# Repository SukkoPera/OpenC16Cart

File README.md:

# OpenC16Cart

OpenC16Cart is an Open Hardware 8/16/32/64 KB Cartridge for the Commodore 16, Plus/4 and the rest of the Commodore 264 family.

## Summary
> Like all the other Commodore 8-bit systems, the Plus/4 had a cartridge port for ROM-based software. Because the computer did not do well in the marketplace, however, very few were released. - Bo Zimmerman

One day I decided to fix my old Commodore 16. I found out about [Diag264](http://www.inchocks.co.uk/commodore/Diag264/) and, since I knew that C16 carts weren't exactly common (to this very day of 2026 I have never seen one "in the flesh"!), I was shocked to learn that [people are deliberately destroying genuine carts to use them as donors to build a Diag264](http://blog.tynemouthsoftware.co.uk/2014/03/commodore-264-c16-and-plus-4-diagnostic.html).

Since I had already built an [Open Hardware cartridge for the Commodore 64](https://github.com/SukkoPera/OpenC64Cart), I thought that one for the C16 could not be much different, and so this project was born.

Since I did not own a cartridge, I set out to find images of PCBs of real cartridges on the Net, only to find out that those are rare as well. In the end I found a couple of [top](https://github.com/SukkoPera/OpenC16Cart/blob/master/doc/inspiration-top.jpg)+[bottom](https://github.com/SukkoPera/OpenC16Cart/blob/master/doc/inspiration-bottom.jpg) images, and started to reverse engineer the design from those. With the help of [some service manuals](http://www.zimmers.net/anonftp/pub/cbm/schematics/computers/plus4/index.html), I came up with OpenC16Cart. I then expanded it to have the ability of using bigger (E(E))PROMs which could store multiple ROM images.

With V5, I even added the possibility of having a single-EEPROM 64 kB cartridge spanning both the C1 and C2 slots.

> [!IMPORTANT]
> V5 is a 44-pin cartridge. It is not compatible with a stock C16/+4. To use it, you will need a [Plus4MultiExpander](https://github.com/SukkoPera/Plus4MultiExpander) [^v4].

V5 was designed in order to fit into [TFW8b's Stumpy Cases](https://www.tfw8b.com/product/commodore-c64-stumpy-cartridge-case/), but the actual fitting has never been checked.

## Configuration
As of V5, OpenC16Cart might work in different modes. Ideally, the cartridge is used with a 64 kb EEPROM, in which case the following configurations will be available:

### 16 kB Mode
In 16 kB mode, you get 4 banks, which can be selected through appropriate placement of the SW2 and SW3 jumpers:

|Bank|SW3|SW2|ROM Area   |
|----|---|---|-----------|
|0   |LO |LO |$0000-$3fff|
|1   |LO |HI |$4000-$7fff|
|2   |HI |LO |$8000-$bfff|
|3   |HI |HI |$c000-$ffff|

Note that the cartridge will respond to all C1 and C2 low/high slots. If this is unwanted, cut open JP1/2/3 accordingly (or do not mount D1/2/3). Also note there is no way to respond to a single C2 slot.

### 32 kB Mode
In 32 kB mode, SW2 must be placed in the `DIR` position and 2 banks will be available through manipulation of SW3:

|Bank|SW3|ROM Area                                      |
|----|---|----------------------------------------------|
|0   |LO |Low ROM: $0000-$3fff<br/>High ROM: $4000-$7fff|
|1   |HI |Low ROM: $8000-$bfff<br/>High ROM: $c000-$ffff|

As in 16 kB mode, you might want to play with the jumpers or diodes.

### 64 kB Mode
In 64 kB mode, both SW2 and SW3 must be placed in the `DIR` position and, obviously, only a single bank will be available.

|Bank|ROM Area                                                                                                    |
|----|------------------------------------------------------------------------------------------------------------|
|0   |C2 Low ROM: $0000-$3fff<br/>C2 High ROM: $4000-$7fff<br>C1 Low ROM: $8000-$bfff<br/>C1 High ROM: $c000-$ffff|

Note that **C2 goes first**.

## Releases
If you want to get this board produced, you are recommended to get [the latest release](https://github.com/SukkoPera/OpenC16Cart/releases) rather than the current git version, as the latter might be under development and is not guaranteed to be working.

Every release is accompanied by its Bill Of Materials (BOM) file and any relevant notes about it, which you are recommended to read carefully.

**I am not providing ready-to-use gerber files**. If all you want is **to get boards made, I would really appreciate if you did so [in a way that supports the project](#support-the-project)**.

## License
The OpenC16Cart documentation, including the design itself, is copyright &copy; SukkoPera 2019-2026 and is licensed under the [Creative Commons Attribution-NonCommercial-ShareAlike 4.0 International License](https://creativecommons.org/licenses/by-nc-sa/4.0/).

This documentation is distributed *as is* and WITHOUT ANY EXPRESS OR IMPLIED WARRANTIES whatsoever with respect to its functionality, operability or use, including, without limitation, any implied warranties OF MERCHANTABILITY, SATISFACTORY QUALITY, FITNESS FOR A PARTICULAR PURPOSE or infringement. We expressly disclaim any liability whatsoever for any direct, indirect, consequential, incidental or special damages, including, without limitation, lost revenues, lost profits, losses resulting from business interruption or loss of data, regardless of the form of action or legal theory under which the liability may be asserted, even if advised of the possibility or likelihood of such damages.

## Support the Project
If you want to get some boards manufactured, you can get them from PCBWay through this link:

You get my gratitude and cheap, professionally-made and good quality PCBs, I get some credit that will help with this and [other projects](https://www.pcbway.com/project/member/shareproject/?bmbid=41100). You won't even have to worry about the various PCB options, it's all pre-configured for you!

Also, if you still have to register, [you can use this link](https://www.pcbway.com/setinvite.aspx?inviteid=41100) to get some bonus initial credit (and yield me some more).

You can also buy me a coffee if you want:

[^v4]: Although this *might* be amended at some point, that's why there currently is no V4, it was reserved for that.

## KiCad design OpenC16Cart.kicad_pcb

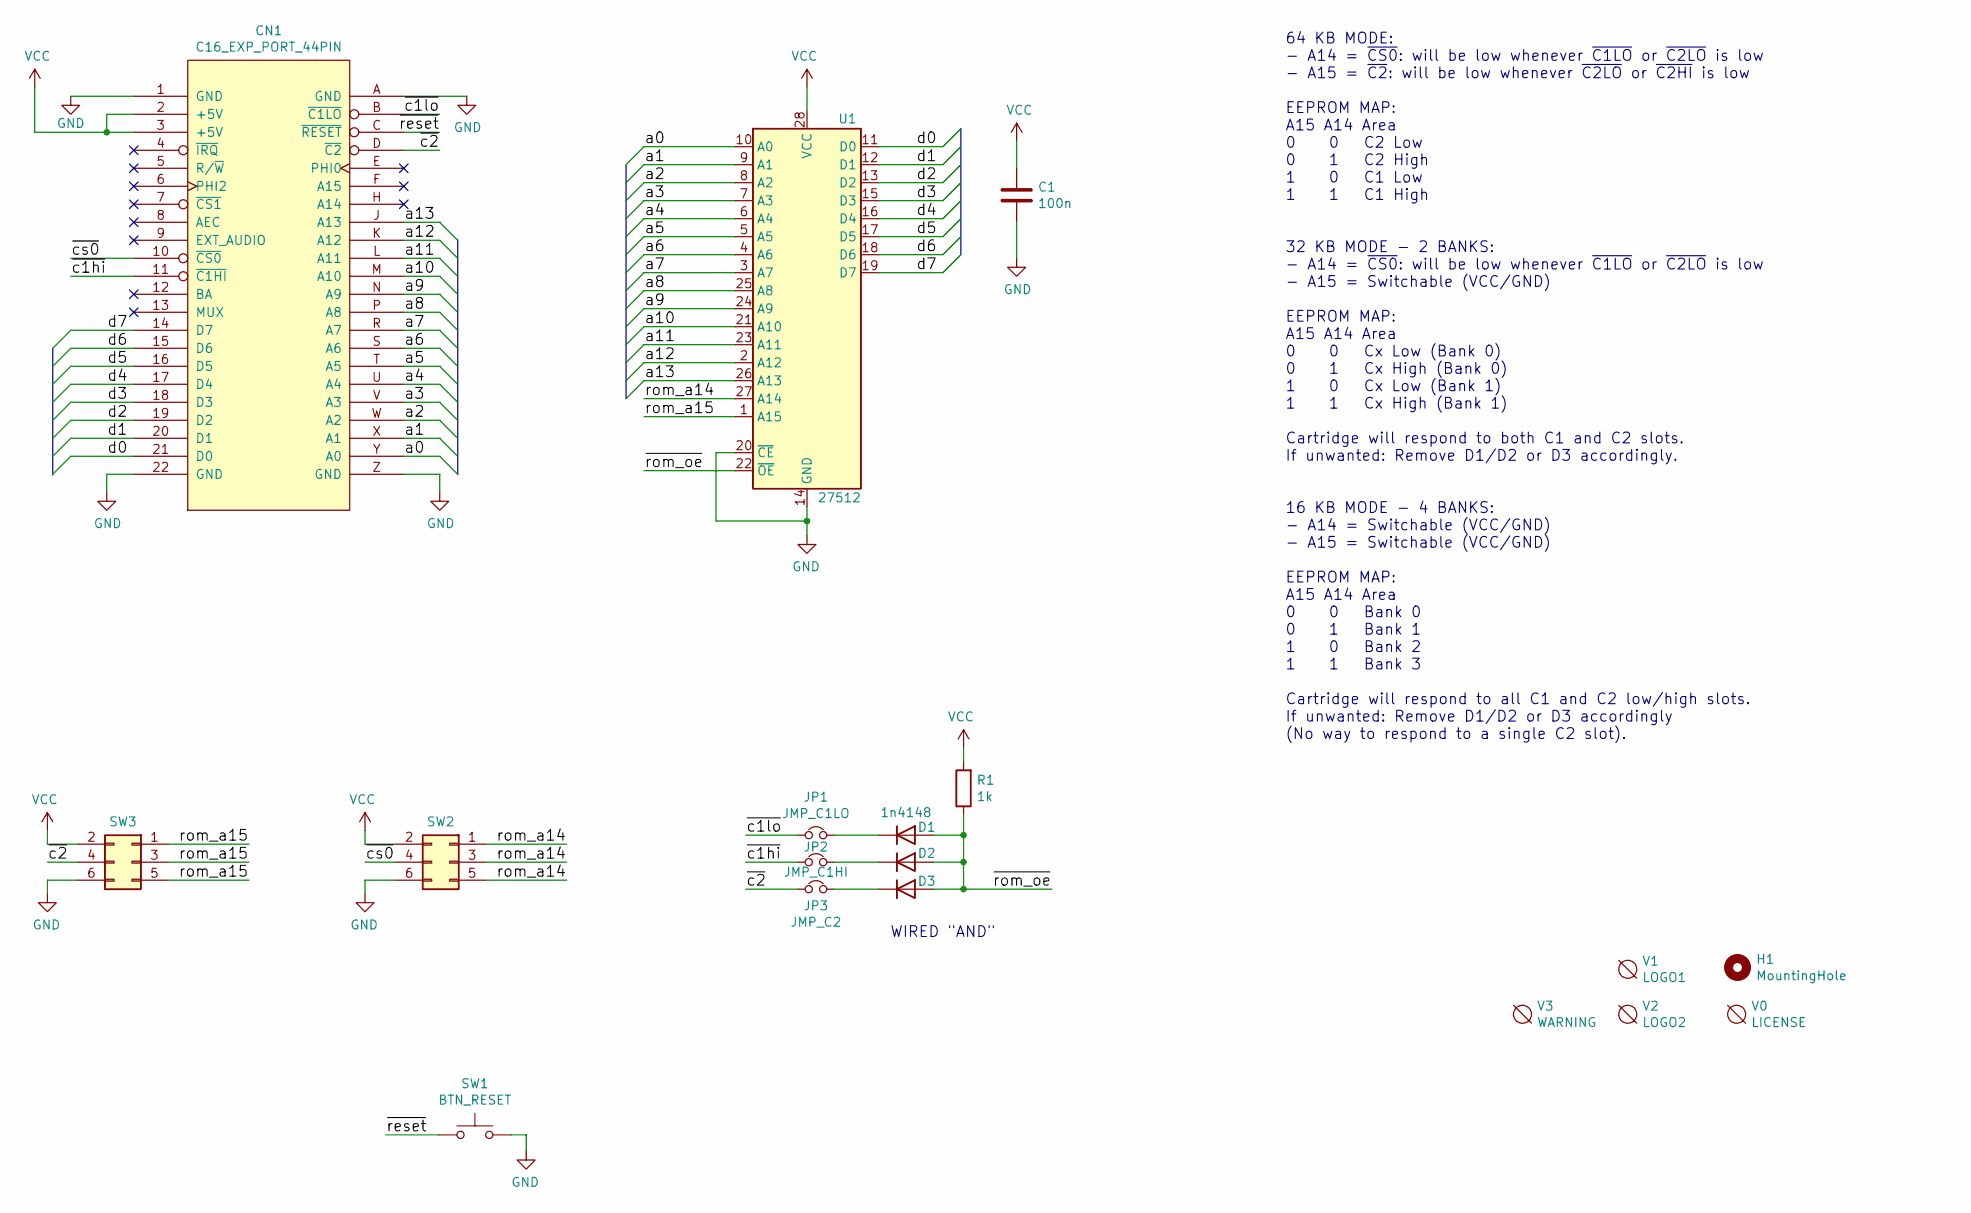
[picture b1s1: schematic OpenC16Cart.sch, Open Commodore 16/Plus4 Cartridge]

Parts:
C1: 100n; C_Disc_D7.0mm_W2.5mm_P5.00mm
CN1: C16_EXP_PORT_44PIN; C16-Exp-Port-44Pin
D1, D2, D3: 1n4148; D_DO-35_SOD27_P7.62mm_Horizontal
H1: MountingHole; MountingHole_5mm
JP1: JMP_C1LO; SolderJumper-2_P1.3mm_Bridged_RoundedPad1.0x1.5mm
JP2: JMP_C1HI; SolderJumper-2_P1.3mm_Bridged_RoundedPad1.0x1.5mm
JP3: JMP_C2; SolderJumper-2_P1.3mm_Bridged_RoundedPad1.0x1.5mm
R1: 1k; R_Axial_DIN0204_L3.6mm_D1.6mm_P7.62mm_Horizontal
SW1: BTN_RESET; SW_PUSH_6mm_H8mm
SW2, SW3: Conn_02x03_Odd_Even; PinHeader_2x03_P2.54mm_Vertical
U1: 27512; DIP-28_W15.24mm_Socket_LongPads
V0: LICENSE; cc_by_nc_sa
V1: LOGO1; logo1
V2: LOGO2; logo2
V3: WARNING; Logo_silk_warning_10x8.5mm

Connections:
/a0: CN1.Y (A0), U1.10 (A0)
/a1: CN1.X (A1), U1.9 (A1)
/a2: CN1.W (A2), U1.8 (A2)
/a3: CN1.V (A3), U1.7 (A3)
/a4: CN1.U (A4), U1.6 (A4)
/a5: CN1.T (A5), U1.5 (A5)
/a6: CN1.S (A6), U1.4 (A6)
/a7: CN1.R (A7), U1.3 (A7)
/a8: CN1.P (A8), U1.25 (A8)
/a9: CN1.N (A9), U1.24 (A9)
/a10: CN1.M (A10), U1.21 (A10)
/a11: CN1.L (A11), U1.23 (A11)
/a12: CN1.K (A12), U1.2 (A12)
/a13: CN1.J (A13), U1.26 (A13)
/d0: CN1.21 (D0), U1.11 (D0)
/d1: CN1.20 (D1), U1.12 (D1)
/d2: CN1.19 (D2), U1.13 (D2)
/d3: CN1.18 (D3), U1.15 (D3)
/d4: CN1.17 (D4), U1.16 (D4)
/d5: CN1.16 (D5), U1.17 (D5)
/d6: CN1.15 (D6), U1.18 (D6)
/d7: CN1.14 (D7), U1.19 (D7)
/rom_a14: SW2.1, SW2.3, SW2.5, U1.27 (A14)
/rom_a15: SW3.1, SW3.3, SW3.5, U1.1 (A15)
/~c1hi: CN1.11 (~C1HI), JP2.1
/~c1lo: CN1.B (~C1LO), JP1.1
/~c2: CN1.D (~C2), JP3.1, SW3.4
/~cs0: CN1.10 (~CS0), SW2.4
/~reset: CN1.C (~RESET), SW1.1
/~rom_oe: D1.2 (A), D2.2 (A), D3.2 (A), R1.1, U1.22 (~OE)
GND: C1.2, CN1.1 (GND), CN1.22 (GND), CN1.A (GND), CN1.Z (GND), SW1.2, SW2.6, SW3.6, U1.14 (GND), U1.20 (~CE)
unnamed: D1.1 (K), JP1.2
unnamed: D2.1 (K), JP2.2
unnamed: D3.1 (K), JP3.2
VCC: C1.1, CN1.2 (+5V), CN1.3 (+5V), R1.2, SW2.2, SW3.2, U1.28 (VCC)

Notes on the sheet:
WIRED "AND"
64 KB MODE: - A14 = ~CS0~: will be low whenever ~C1LO~ or ~C2LO~ is low - A15 = ~C2~: will be low whenever ~C2LO~ or ~C2HI~ is low EEPROM MAP: A15 A14 Area 0 0 C2 Low 0 1 C2 High 1 0 C1 Low 1 1 C1 High 32 KB MODE - 2 BANKS: - A14 = ~CS0~: will be low whenever ~C1LO~ or ~C2LO~ is low - A15 = Switcha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

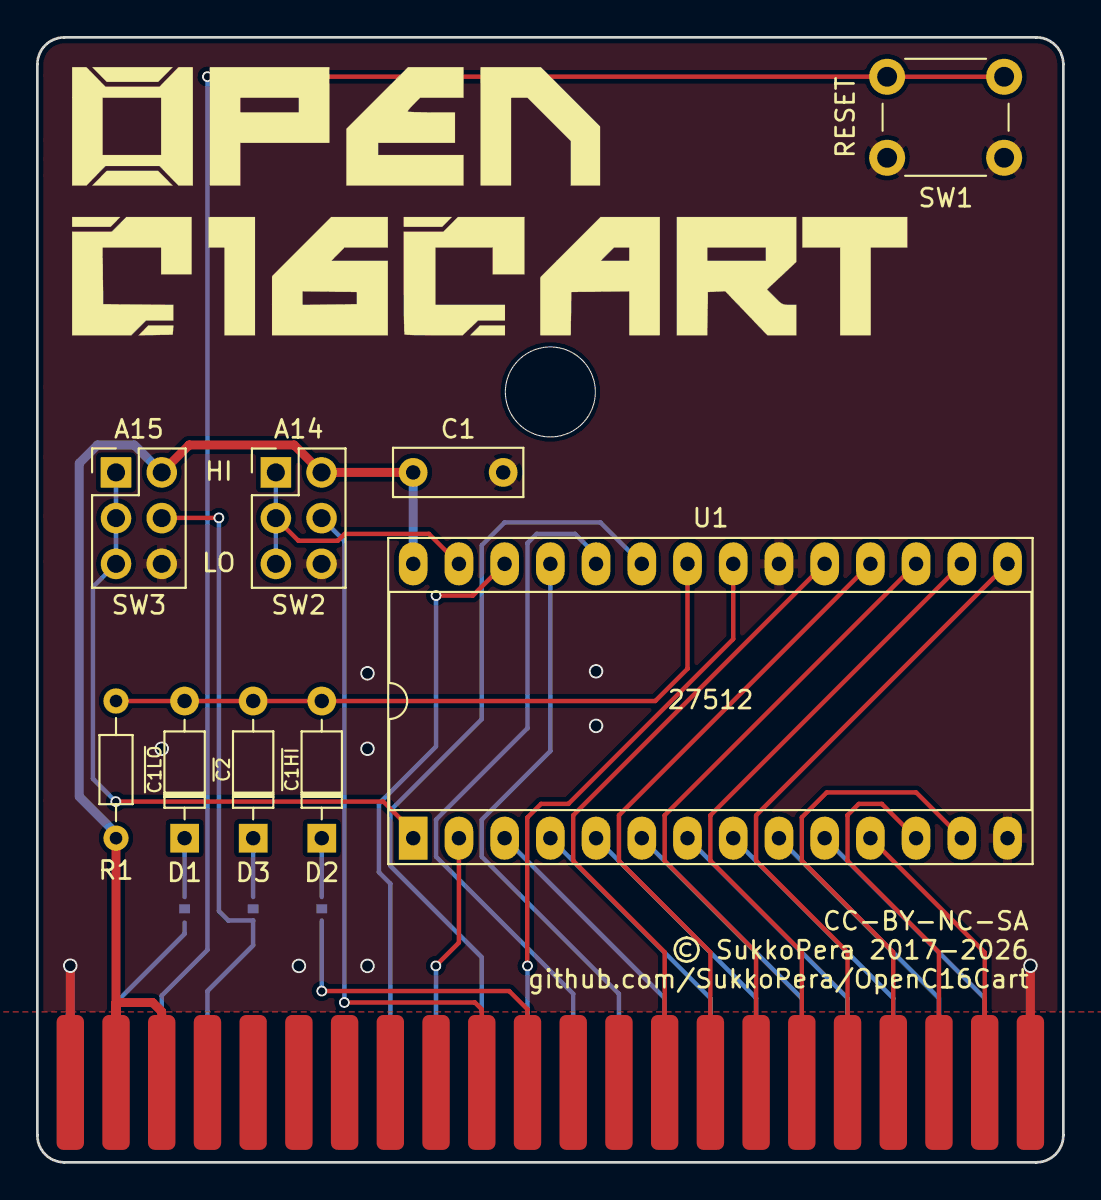
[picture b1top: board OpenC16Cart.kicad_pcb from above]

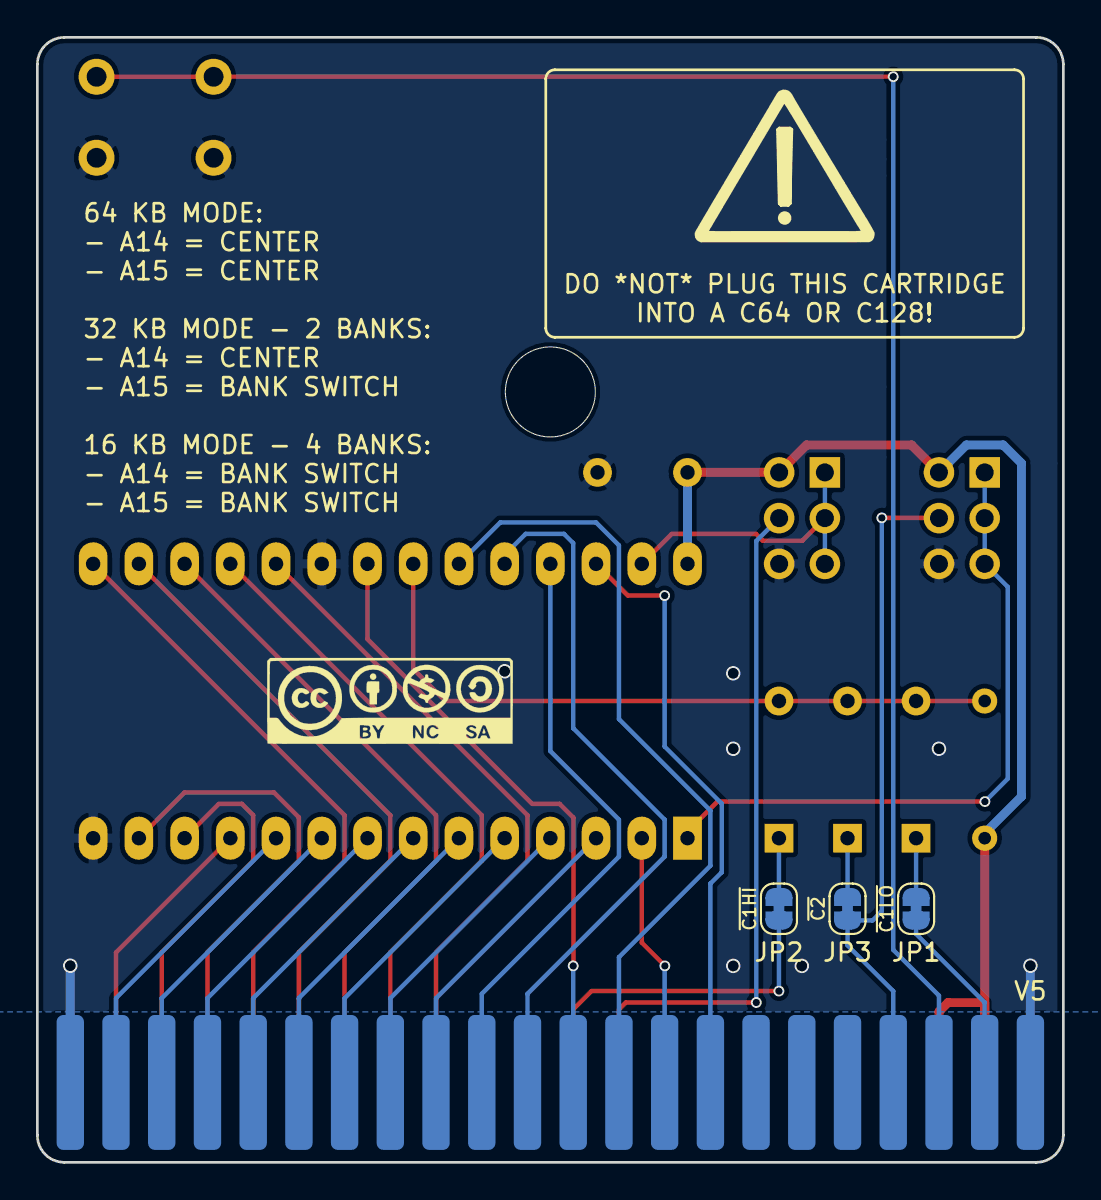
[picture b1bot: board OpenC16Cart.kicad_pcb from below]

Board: 2 copper layers, 57.0 x 62.5 mm, 18 parts (5 on the bottom side), 35 nets.

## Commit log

2017-09-01 Add cart connector footprint
2017-09-01 Ignore more backup files and gerbers
2017-09-02 V2 is almost ready!
2017-09-02 Make board slightly larger
2017-09-02 Add OSHW logo
2017-09-29 Switch to C_0805_HandSoldering and rebuild whatever is needed
2017-09-30 Space edge connector pins 2.0mm apart
2017-09-30 Tighter soldermask
2017-09-30 Make top corners smooth
2017-09-30 Simplify ROM silkscreen
2017-09-30 Fix 3D models
2017-09-30 Bump version
2017-10-02 Add renders and reorder inspirational images
2018-01-01 Minor tweaks'n'fixes
2018-01-07 Final touches for V3
2020-11-02 Fix Diag264 link
2023-07-30 Port to KiCad 5 - NOT YET USABLE!
2023-07-30 Much better
2023-07-30 Honing
2023-07-30 Experimental 16/32/64 KB version with 44-pin 2.54" connector
2023-07-30 Add logo
2023-08-03 Comply with Stumpy cases dimensions
2023-08-03 Add reset button
2023-08-03 Bigger logo and final touches
2023-08-03 Make hole compliant with Stumpy cases
2023-09-07 Fix R1 value and A14/15 labels
2023-09-10 Move components bottom left
2023-10-03 Switch to new pinout
2026-03-09 Update README and renders
2026-03-09 Ready for V5

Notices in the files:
OpenC16Cart.kicad_pcb:
© SukkoPera 2017-2026
